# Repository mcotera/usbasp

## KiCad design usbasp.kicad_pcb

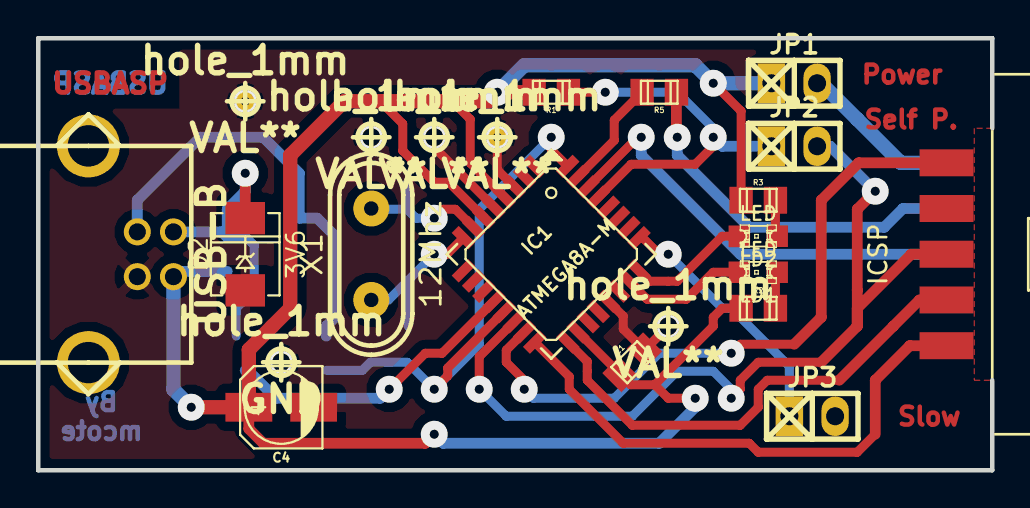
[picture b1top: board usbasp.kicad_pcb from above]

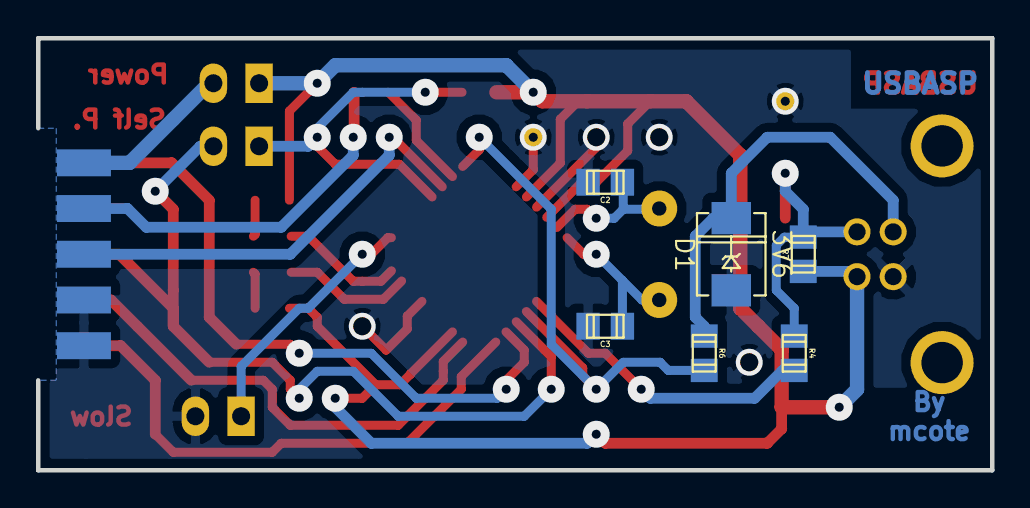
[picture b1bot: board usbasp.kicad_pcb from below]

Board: 2 copper layers, 53.0 x 24.0 mm, 28 parts (6 on the bottom side), 22 nets.

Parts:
C1: 100n; c_0805
C2, C3: 22p; c_0805
C4: 4u7; c_elec_4x5.3
D1, D2: 3V6; DO-214AA(SMB)
IC1: ATMEGA8A-M; lqfp32
J1: ICSP; vasch_strip_5x2_vert_MC
JP1: POWER; pin_socket_2
JP2: Self P.; pin_socket_2
JP3: SLOW; pin_socket_2
JP4: USB-B; conn_usb_B
LD1, LD2: LED; LED-0805
R1: 10K; r_0805
R2, R3: 1.5K; r_0805
R4, R6: 68; r_0805
R5: 1K; r_0805
R7: 2K2; r_0805
X1: 12Mhz; crystal_hc-49s
hole_1mm, hole_1mm#3, hole_1mm#4, hole_1mm#5, hole_1mm#6: VAL**; hole_1mm
hole_1mm#2: GND; hole_1mm

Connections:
+5V: C1.2, C4.1, IC1.4, IC1.6, IC1.18, JP1.1, JP4.1, R1.1, R2.2, R3.2, R7.2
/MISO: IC1.16, J1.9
/MOSI: IC1.15, J1.1
/RXD: IC1.30, J1.6
/SCK: IC1.17, J1.7
/SLOW: IC1.25, JP3.1
/SS: IC1.14, J1.5, JP2.2
/TXD: J1.4, R5.2
/VCCINT: J1.2, JP1.2
GND: C1.1, C2.1, C3.1, C4.2, D1.1, D2.1, IC1.3, IC1.5, IC1.21, J1.8, J1.10, JP3.2, JP4.4, hole_1mm.1, hole_1mm#2.1, hole_1mm#3.1, hole_1mm#4.1, hole_1mm#5.1, hole_1mm#6.1
unnamed: IC1.23, LD1.2
unnamed: IC1.24, LD2.2
unnamed: D1.2, JP4.3, R6.2
unnamed: D2.2, JP4.2, R4.2, R7.1
unnamed: LD2.1, R3.1
unnamed: LD1.1, R2.1
unnamed: IC1.12, R4.1
unnamed: IC1.31, R5.1
unnamed: IC1.13, IC1.32, R6.1
unnamed: IC1.29, JP2.1, R1.2
unnamed: C2.2, IC1.7, X1.2
unnamed: C3.2, IC1.8, X1.1

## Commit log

2017-09-08 add dile of proyect
